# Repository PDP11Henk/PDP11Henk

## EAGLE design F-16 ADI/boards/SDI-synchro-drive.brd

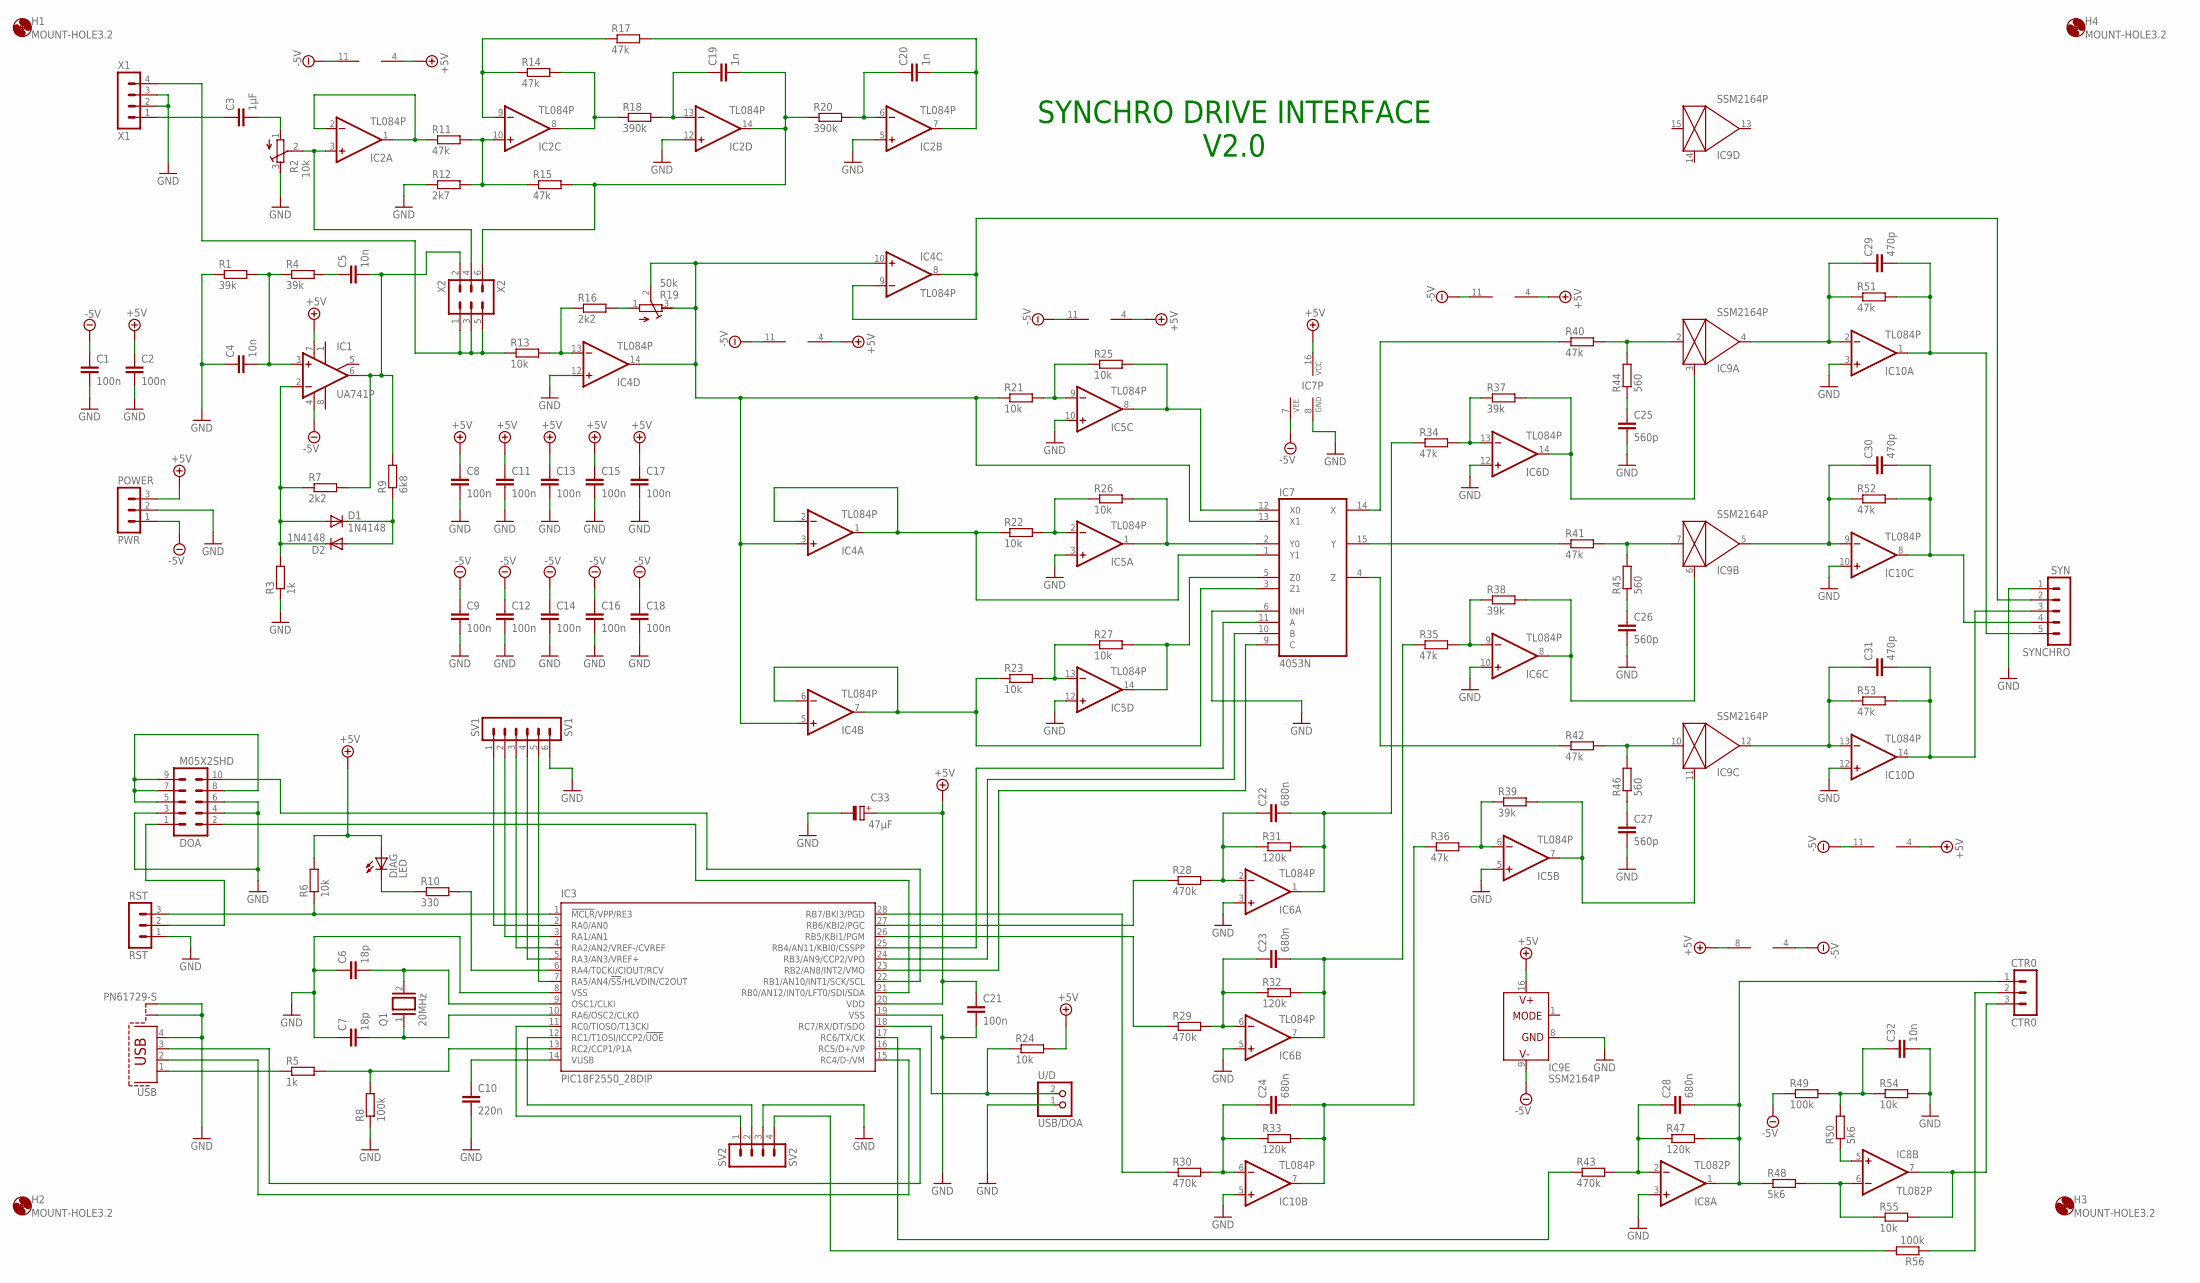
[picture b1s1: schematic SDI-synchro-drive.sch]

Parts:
C1, C2, C8, C9, C11, C12, C13, C14, C15, C16, C17, C18, C21: 100n; C025-025X050
C3: 1µF; C5B3
C4, C5, C32: 10n; C025-025X050
C6, C7: 18p; C025-025X050
C10: 220n; C5B3
C19, C20: 1n; C025-025X050
C22, C23, C24, C28: 680n; C5B3
C25, C26, C27: 560p; C025-025X050
C29, C30, C31: 470p; C025-025X050
C33: 47µF; E2,5-6
CTR0: CTR0; MA03-1
D1, D2: 1N4148; DO35-7
DIAG: LED; LED3MM
DOA: M05X2SHD; 2X5-SHROUDED
H1, H2, H3, H4: MOUNT-HOLE3.2; 3,2
IC1: UA741P; DIL08
IC2, IC4, IC5, IC6, IC10: TL084P; DIL14
IC3: PIC18F2550_28DIP; DIL28-3
IC7: 4053N; DIL16
IC8: TL082P; DIL08
IC9: SSM2164P; DIL16
POWER: PWR; MA03-1
Q1: 20MHz; QS
R1, R4, R37, R38, R39: 39k; 0204/7
R2: 10k; RTRIM3299W
R3, R5: 1k; 0204/7
R6, R13, R21, R22, R23, R24, R25, R26, R27, R54, R55: 10k; 0204/7
R7, R16: 2k2; 0204/7
R8, R49, R56: 100k; 0204/7
R9: 6k8; 0204/7
R10: 330; 0204/7
R11, R14, R15, R17, R34, R35, R36, R40, R41, R42, R51, R52, R53: 47k; 0204/7
R12: 2k7; 0204/7
R18, R20: 390k; 0204/7
R19: 50k; RTRIM3299W
R28, R29, R30, R43: 470k; 0204/7
R31, R32, R33, R47: 120k; 0204/7
R44, R45, R46: 560; 0204/7
R48, R50: 5k6; 0204/7
RST: RST; MA03-1
SV1: SV1; MA06-1
SV2: SV2; MA04-1
SYNCHRO: SYN; MA05-1
USB: PN61729-S
USB/DOA: U/D; 1X02
X1: X1; MA04-1
X2: X2; MA03-2

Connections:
+5V: C2.1, C8.1, C11.1, C13.1, C15.1, C17.1, C21.1, C33.+, DIAG.A, IC1.7 (V+), IC2.4 (V+), IC3.20 (VDD), IC4.4 (V+), IC5.4 (V+), IC6.4 (V+), IC7.16 (VCC), IC8.8 (V+), IC9.16 (V+), IC10.4 (V+), POWER.3, R6.2, R24.2
-5V: C1.1, C9.1, C12.1, C14.1, C16.1, C18.1, IC1.4 (V-), IC2.11 (V-), IC4.11 (V-), IC5.11 (V-), IC6.11 (V-), IC7.7 (VEE), IC8.4 (V-), IC9.9 (V-), IC10.11 (V-), POWER.1, R49.1
GND: C1.2, C2.2, C4.1, C6.1, C7.1, C8.2, C9.2, C10.2, C11.2, C12.2, C13.2, C14.2, C15.2, C16.2, C17.2, C18.2, C21.2, C25.2, C26.2, C27.2, C32.2, C33.-, DOA.3, DOA.4, DOA.6, IC2.5 (+IN), IC2.12 (+IN), IC3.8 (VSS), IC3.19 (VSS), IC4.12 (+IN), IC5.3 (+IN), IC5.5 (+IN), IC5.10 (+IN), IC5.12 (+IN), IC6.3 (+IN), IC6.5 (+IN), IC6.10 (+IN), IC6.12 (+IN), IC7.6 (INH), IC7.8 (GND), IC8.3 (+IN), IC9.8 (GND), IC10.3 (+IN), IC10.5 (+IN), IC10.10 (+IN), IC10.12 (+IN), POWER.2, R1.1, R2.3 (A), R3.1, R8.1, R12.1, R54.2, RST.1, SV1.6, SV2.3, SYNCHRO.1, USB.4, USB.S1, USB.S2, USB/DOA.1, X1.2, X1.3
unnamed: IC8.6 (-IN), R48.2, R55.1
unnamed: CTR0.3, IC8.7 (OUT), R55.2
unnamed: C3.2, R2.1 (E)
unnamed: IC2.3 (+IN), R2.2 (S), X2.4
unnamed: IC2.1 (OUT), IC2.2 (-IN), R11.1
unnamed: IC2.10 (+IN), R11.2, R12.2, R15.1
unnamed: C20.1, IC2.6 (-IN), R20.2
unnamed: IC2.9 (-IN), R14.1, R17.1
unnamed: IC2.8 (OUT), R14.2, R18.1
unnamed: C19.1, IC2.13 (-IN), R18.2
unnamed: C19.2, IC2.14 (OUT), R15.2, R20.1, X2.6
unnamed: C20.2, IC2.7 (OUT), R17.2
unnamed: R13.1, X1.4, X2.1, X2.3, X2.5
unnamed: IC4.13 (-IN), R13.2, R16.1
unnamed: R16.2, R19.1 (E)
unnamed: IC5.13 (-IN), R23.2, R27.1
unnamed: IC4.8 (OUT), IC4.9 (-IN), SYNCHRO.2
unnamed: CTR0.2, R56.1
unnamed: IC5.2 (-IN), R22.2, R26.1
unnamed: C5.2, IC1.6 (OUT), R7.2, R9.2, X2.2
unnamed: IC5.9 (-IN), R21.2, R25.1
unnamed: C5.1, R4.2
unnamed: IC5.8 (OUT), IC7.12 (X0), R25.2
unnamed: IC5.1 (OUT), IC7.2 (Y0), R26.2
unnamed: C4.2, IC1.3 (+IN), R1.2, R4.1
unnamed: IC5.14 (OUT), IC7.5 (Z0), R27.2
unnamed: D1.A, D2.C, IC1.2 (-IN), R3.2, R7.1
unnamed: D1.C, D2.A, R9.1
unnamed: IC7.14 (X), R40.1
unnamed: IC9.2 (IN), R40.2, R44.2
unnamed: IC7.15 (Y), R41.1
unnamed: IC9.7 (IN), R41.2, R45.2
unnamed: IC7.4 (Z), R42.1
unnamed: IC9.10 (IN), R42.2, R46.2
unnamed: C25.1, R44.1
unnamed: C26.1, R45.1
unnamed: C27.1, R46.1
unnamed: IC5.6 (-IN), R36.2, R39.1
unnamed: IC5.7 (OUT), IC9.11 (CTRL), R39.2
unnamed: IC6.14 (OUT), IC9.3 (CTRL), R37.2
unnamed: IC6.8 (OUT), IC9.6 (CTRL), R38.2
unnamed: IC6.9 (-IN), R35.2, R38.1
unnamed: IC6.13 (-IN), R34.2, R37.1
unnamed: C22.1, IC6.2 (-IN), R28.2, R31.1
unnamed: C22.2, IC6.1 (OUT), R31.2, R34.1
unnamed: C23.1, IC6.6 (-IN), R29.2, R32.1
unnamed: C23.2, IC6.7 (OUT), R32.2, R35.1
unnamed: C10.1, IC3.14 (VUSB)
unnamed: C24.1, IC10.6 (-IN), R30.2, R33.1
unnamed: C24.2, IC10.7 (OUT), R33.2, R36.1
unnamed: IC3.16 (RC5/D+/VP), USB.3
unnamed: C29.1, IC9.4 (OUT), IC10.2 (-IN), R51.1
unnamed: C29.2, IC10.1 (OUT), R51.2, SYNCHRO.5
unnamed: C30.1, IC9.5 (OUT), IC10.9 (-IN), R52.1
unnamed: C30.2, IC10.8 (OUT), R52.2, SYNCHRO.4
unnamed: C31.1, IC9.12 (OUT), IC10.13 (-IN), R53.1
unnamed: C31.2, IC10.14 (OUT), R53.2, SYNCHRO.3
unnamed: IC3.15 (RC4/D-/VM), USB.2
unnamed: R5.1, USB.1
unnamed: IC3.13 (RC2/CCP1/P1A), R5.2, R8.2
unnamed: DOA.1, RST.2
unnamed: C7.2, IC3.10 (RA6/OSC2/CLKO), Q1.1
unnamed: C6.2, IC3.9 (OSC1/CLKI), Q1.2
unnamed: IC3.1 (!MCLR!/VPP/RE3), R6.1, RST.3
unnamed: IC3.28 (RB7/BKI3/PGD), R30.1
unnamed: IC3.26 (RB5/KBI1/PGM), R29.1
unnamed: IC3.27 (RB6/KBI2/PGC), R28.1
unnamed: DOA.5, DOA.7, DOA.8, DOA.9
unnamed: DOA.2, IC3.21 (RB0/AN12/INT0/LFT0/SDI/SDA)
unnamed: DIAG.K (C), R10.1
unnamed: IC3.6 (RA4/T0CKI/CIOUT/RCV), R10.2
unnamed: DOA.10, IC3.22 (RB1/AN10/INT1/SCK/SCL)
unnamed: IC3.18 (RC7/RX/DT/SDO), R24.1, USB/DOA.2
unnamed: IC3.12 (RC1/T1OSI/ICCP2/!UOE), SV2.2
unnamed: IC3.25 (RB4/AN11/KBI0/CSSPP), IC7.11 (A)
unnamed: IC3.24 (RB3/AN9/CCP2/VPO), IC7.10 (B)
unnamed: IC3.23 (RB2/AN8/INT2/VMO), IC7.9 (C)
unnamed: IC3.2 (RA0/AN0), SV1.1
unnamed: IC3.3 (RA1/AN1), SV1.2
unnamed: IC3.4 (RA2/AN2/VREF-/CVREF), SV1.3
unnamed: IC3.5 (RA3/AN3/VREF+), SV1.4
unnamed: IC3.7 (RA5/AN4/!SS!/HLVDIN/C2OUT), SV1.5
unnamed: IC3.11 (RC0/TIOSO/T13CKI), SV2.1
unnamed: IC3.17 (RC6/TX/CK), R43.1
unnamed: C28.1, IC8.2 (-IN), R43.2, R47.1
unnamed: C28.2, CTR0.1, IC8.1 (OUT), R47.2, R48.1
unnamed: C32.1, R49.2, R50.2, R54.1
unnamed: IC8.5 (+IN), R50.1
unnamed: C3.1, X1.1
unnamed: R56.2, SV2.4
SIN000: IC4.3 (+IN), IC4.5 (+IN), IC4.10 (+IN), IC4.14 (OUT), IC7.13 (X1), R19.2 (S), R19.3 (A), R21.1
SIN120: IC4.1 (OUT), IC4.2 (-IN), IC7.1 (Y1), R22.1
SIN240: IC4.6 (-IN), IC4.7 (OUT), IC7.3 (Z1), R23.1

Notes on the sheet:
SYNCHRO DRIVE INTERFACE V2.0

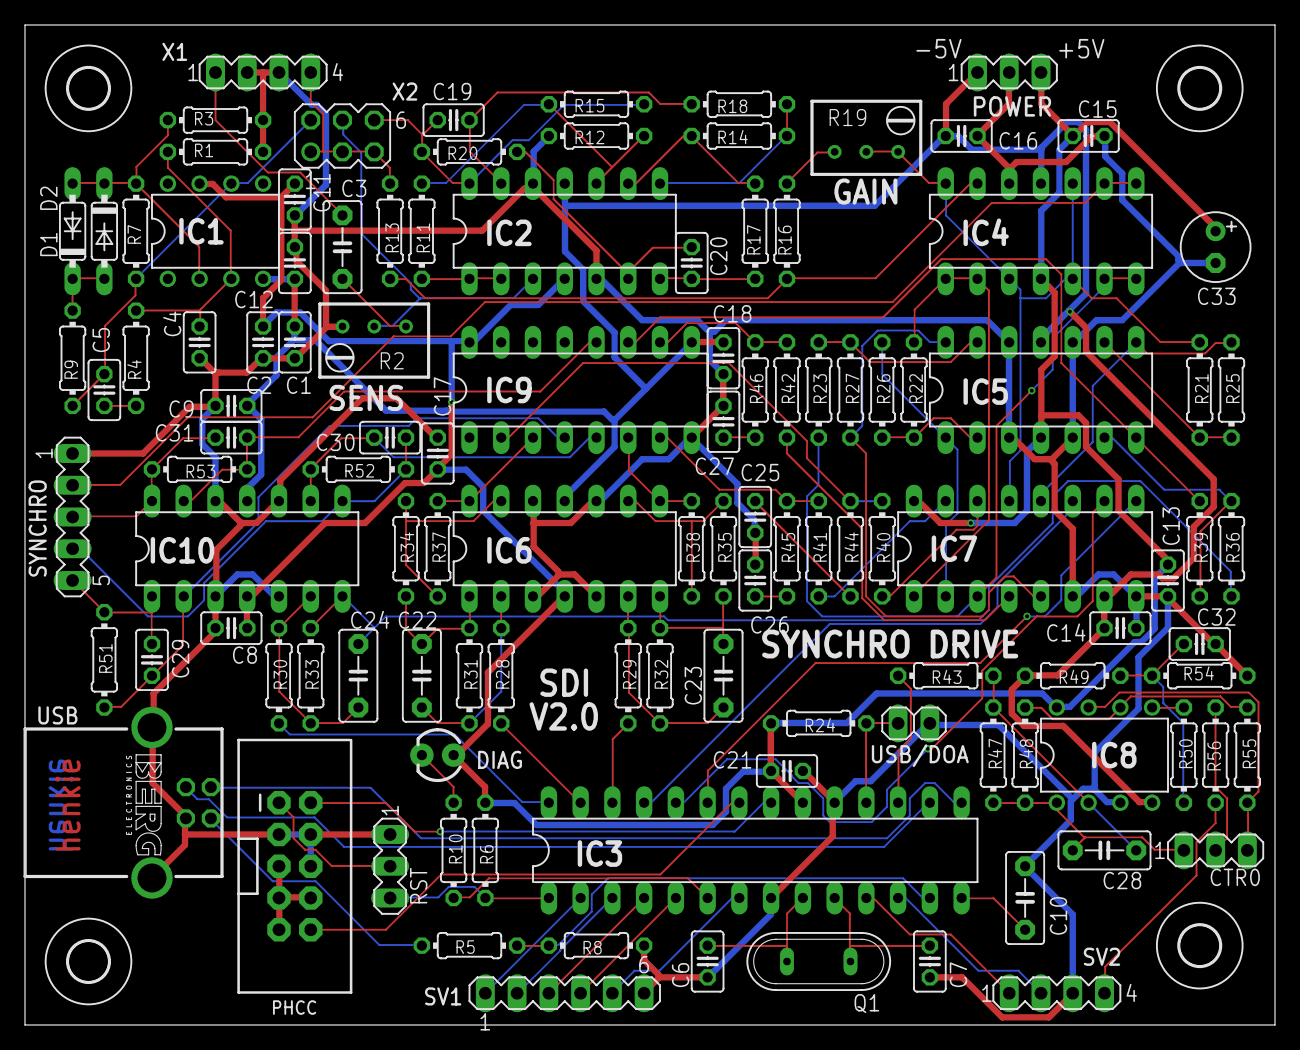
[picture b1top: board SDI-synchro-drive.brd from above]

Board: 2 copper layers, 100.0 x 80.0 mm, 118 parts (0 on the bottom side), 96 nets.

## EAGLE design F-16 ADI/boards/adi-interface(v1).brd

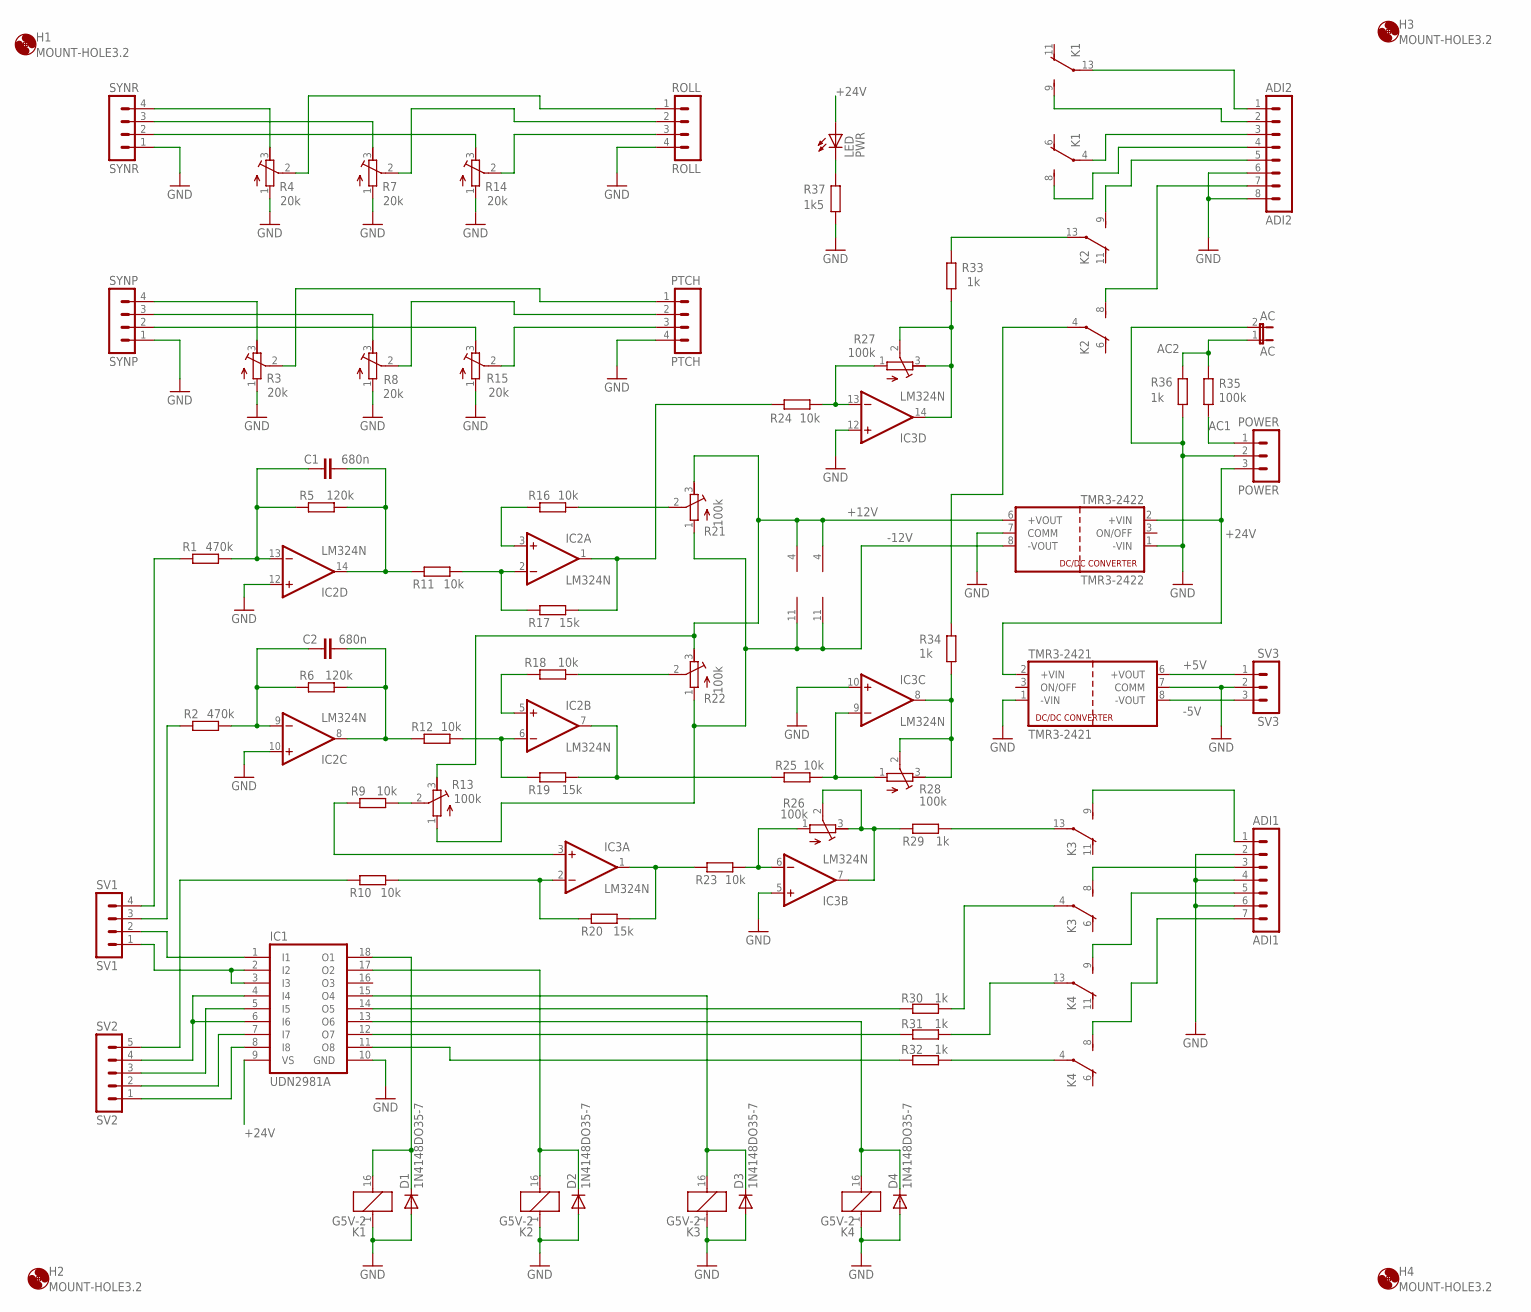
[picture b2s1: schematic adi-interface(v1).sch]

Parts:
AC: AC; 1X02
ADI1: ADI1; MA07-1
ADI2: ADI2; MA08-1
C1, C2: 680n; C050-035X075
D1, D2, D3, D4: 1N4148DO35-7; DO35-7
H1, H2, H3, H4: MOUNT-HOLE3.2; 3,2
IC1: UDN2981A; DIL18
IC2, IC3: LM324N; DIL14
K1, K2, K3, K4: G5V-2
LED: PWR; LED3MM
POWER: POWER; MA03-1
PTCH: PTCH; MA04-1
R1, R2: 470k; 0204/7
R3, R4, R7, R8, R14, R15: 20k; RTRIM64Z
R5, R6: 120k; 0204/7
R9, R10, R11, R12, R16, R18, R23, R24, R25: 10k; 0204/7
R13, R21, R22, R26, R27, R28: 100k; RTRIM64Z
R17, R19, R20: 15k; 0204/7
R29, R30, R31, R32, R33, R34, R36: 1k; 0204/7
R35: 100k; 0204/7
R37: 1k5; 0204/7
ROLL: ROLL; MA04-1
SV1: SV1; MA04-1
SV2: SV2; MA05-1
SV3: SV3; MA03-1
SYNP: SYNP; MA04-1
SYNR: SYNR; MA04-1
TMR3-2421: TMR3-2421; TRACO_SIP-8
TMR3-2422: TMR3-2422; TRACO_SIP-8

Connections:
+5V: SV3.1, TMR3-2421.6 (+VOUT)
+12V: IC2.4 (V+), IC3.4 (V+), R13.3 (E), R21.3 (E), R22.3 (E), TMR3-2422.6 (+VOUT)
+24V: IC1.9 (VS), LED.A, POWER.3, TMR3-2421.2 (+VIN), TMR3-2422.2 (+VIN)
-5V: SV3.3, TMR3-2421.8 (-VOUT)
-12V: IC2.11 (V-), IC3.11 (V-), R13.1 (A), R21.1 (A), R22.1 (A), TMR3-2422.8 (-VOUT)
AC1: POWER.1, R35.1
AC2: AC.1, R35.2, R36.2
GND: AC.2, ADI1.2, ADI1.4, ADI1.6, ADI2.6, ADI2.8, D1.A, D2.A, D3.A, D4.A, IC1.10 (GND), IC2.10 (+IN), IC2.12 (+IN), IC3.5 (+IN), IC3.10 (+IN), IC3.12 (+IN), K1.1, K2.1, K3.1, K4.1, POWER.2, PTCH.4, R3.1 (A), R4.1 (A), R7.1 (A), R8.1 (A), R14.1 (A), R15.1 (A), R36.1, R37.1, ROLL.4, SV3.2, SYNP.1, SYNR.1, TMR3-2421.1 (-VIN), TMR3-2421.7 (COMM), TMR3-2422.1 (-VIN), TMR3-2422.7 (COMM)
unnamed: R14.3 (E), SYNR.2
unnamed: R7.3 (E), SYNR.3
unnamed: R4.3 (E), SYNR.4
unnamed: R3.3 (E), SYNP.4
unnamed: R8.3 (E), SYNP.3
unnamed: R15.3 (E), SYNP.2
unnamed: R14.2 (S), ROLL.3
unnamed: R7.2 (S), ROLL.2
unnamed: R4.2 (S), ROLL.1
unnamed: PTCH.3, R15.2 (S)
unnamed: PTCH.2, R8.2 (S)
unnamed: PTCH.1, R3.2 (S)
unnamed: ADI2.1, K1.13
unnamed: ADI2.2, K1.9 (S)
unnamed: ADI2.3, K1.4
unnamed: ADI2.4, K1.8 (S)
unnamed: ADI2.5, K2.9 (S)
unnamed: ADI2.7, K2.8 (S)
unnamed: D1.C, IC1.18 (O1), K1.16 (2)
unnamed: ADI1.1, K3.9 (S)
unnamed: D2.C, IC1.17 (O2), K2.16 (2)
unnamed: ADI1.3, K3.8 (S)
unnamed: ADI1.5, K4.9 (S)
unnamed: ADI1.7, K4.8 (S)
unnamed: K3.4, R30.2
unnamed: K4.13, R31.2
unnamed: IC1.2 (I2), IC1.3 (I3), SV1.1
unnamed: IC1.1 (I1), SV1.2
unnamed: K4.4, R32.2
unnamed: D4.C, IC1.13 (O6), K4.16 (2)
unnamed: D3.C, IC1.15 (O4), K3.16 (2)
unnamed: IC1.11 (O8), R32.1
unnamed: IC1.12 (O7), R31.1
unnamed: R2.1, SV1.3
unnamed: C2.1, IC2.9 (-IN), R2.2, R6.1
unnamed: C2.2, IC2.8 (OUT), R6.2, R12.1
unnamed: R1.1, SV1.4
unnamed: IC2.2 (-IN), R11.2, R17.1
unnamed: C1.2, IC2.14 (OUT), R5.2, R11.1
unnamed: C1.1, IC2.13 (-IN), R1.2, R5.1
unnamed: K2.13, R33.2
unnamed: IC2.1 (OUT), R17.2, R24.1
unnamed: IC2.6 (-IN), R12.2, R19.1
unnamed: K2.4, R34.2
unnamed: IC2.7 (OUT), R19.2, R25.1
unnamed: IC2.3 (+IN), R16.1
unnamed: IC2.5 (+IN), R18.1
unnamed: R16.2, R21.2 (S)
unnamed: R18.2, R22.2 (S)
unnamed: LED.K (C), R37.2
unnamed: IC3.6 (-IN), R23.2, R26.1 (A)
unnamed: IC3.7 (OUT), R26.2 (S), R26.3 (E), R29.1
unnamed: IC3.13 (-IN), R24.2, R27.1 (A)
unnamed: K3.13, R29.2
unnamed: IC3.1 (OUT), R20.2, R23.1
unnamed: IC3.14 (OUT), R27.2 (S), R27.3 (E), R33.1
unnamed: R9.2, R13.2 (S)
unnamed: IC3.9 (-IN), R25.2, R28.1 (A)
unnamed: IC3.8 (OUT), R28.2 (S), R28.3 (E), R34.1
unnamed: IC3.3 (+IN), R9.1
unnamed: R10.1, SV2.5
unnamed: IC3.2 (-IN), R10.2, R20.1
unnamed: IC1.14 (O5), R30.1
unnamed: IC1.4 (I4), IC1.6 (I6), SV2.4
unnamed: IC1.5 (I5), SV2.3
unnamed: IC1.7 (I7), SV2.2
unnamed: IC1.8 (I8), SV2.1

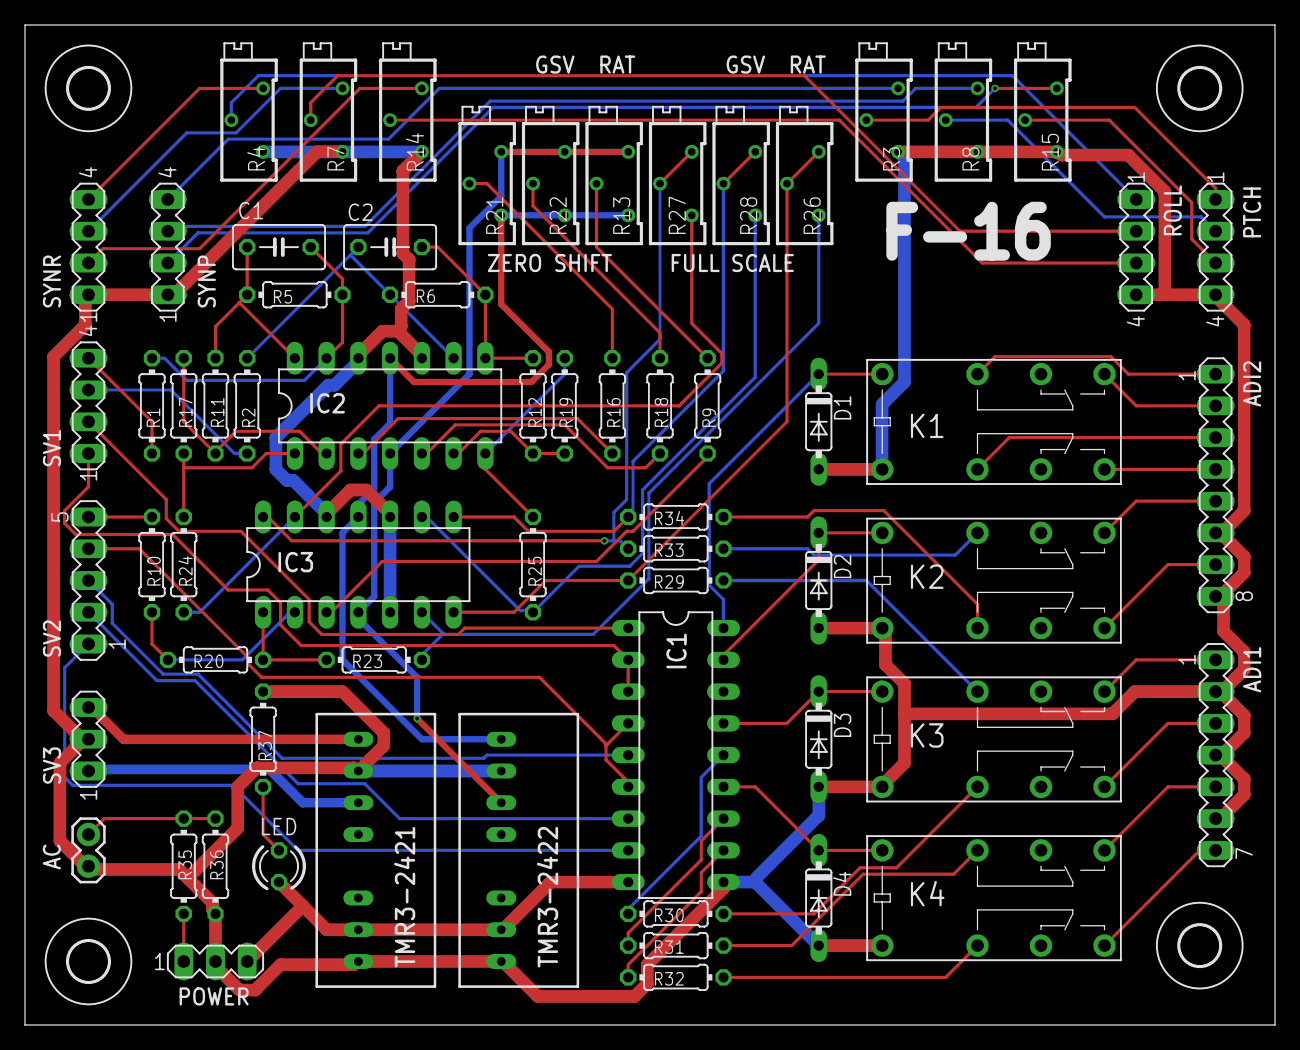
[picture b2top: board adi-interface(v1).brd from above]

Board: 2 copper layers, 100.0 x 80.0 mm, 68 parts (0 on the bottom side), 75 nets.

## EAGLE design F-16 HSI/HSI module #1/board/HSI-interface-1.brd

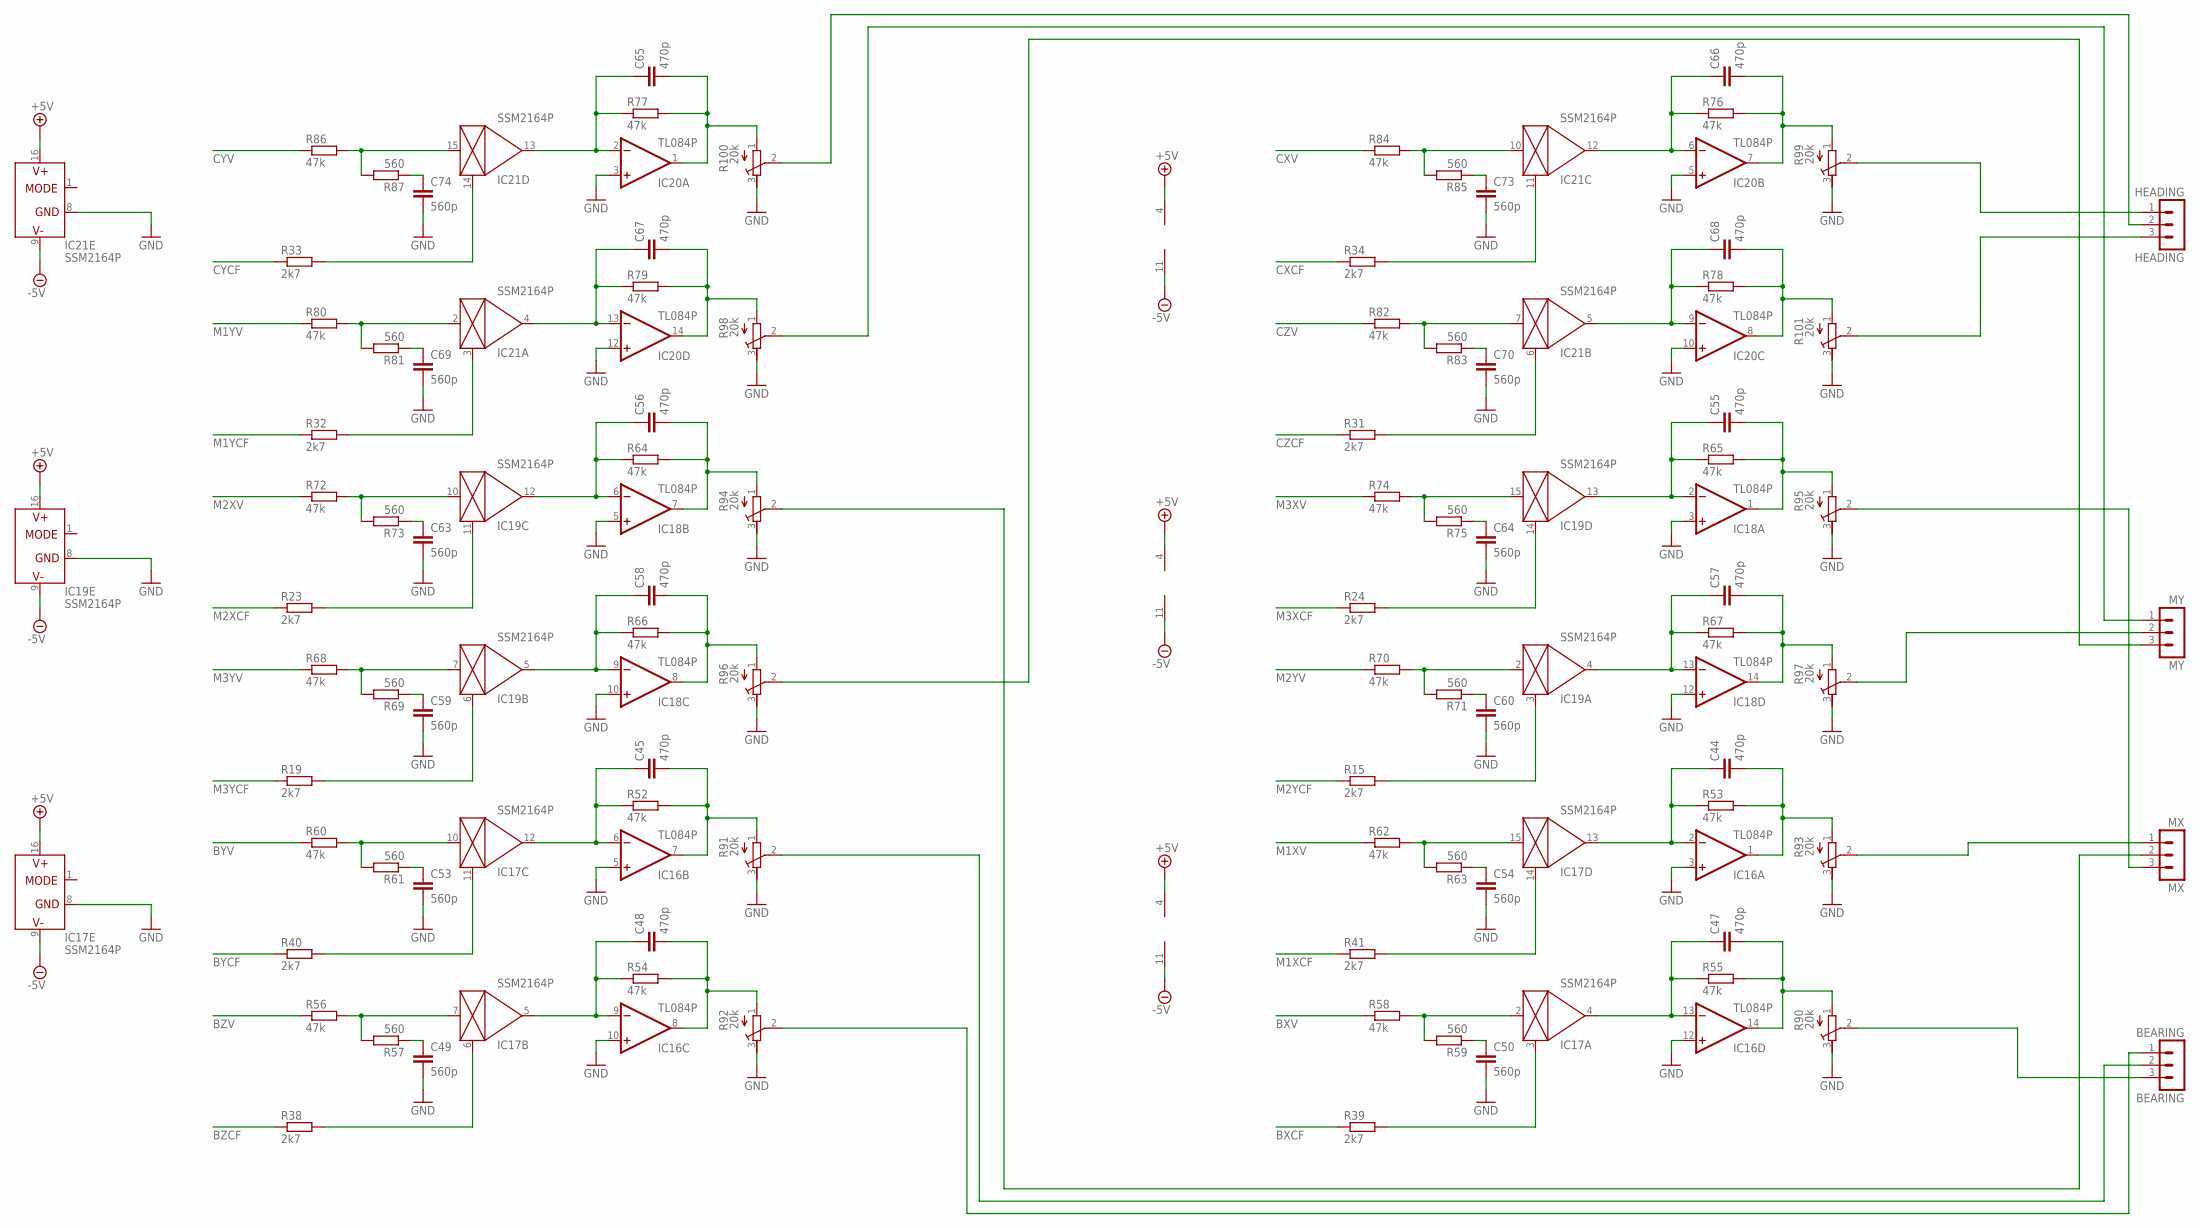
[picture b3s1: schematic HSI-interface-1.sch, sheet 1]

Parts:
BEARING: BEARING; MA03-1
C44, C45, C47, C48, C55, C56, C57, C58, C65, C66, C67, C68: 470p; C025-025X050
C49, C50, C53, C54, C59, C60, C63, C64, C69, C70, C73, C74: 560p; C025-025X050
HEADING: HEADING; MA03-1
IC16, IC18, IC20: TL084P; DIL14
IC17, IC19, IC21: SSM2164P; DIL16
MX: MX; MA03-1
MY: MY; MA03-1
R15, R19, R23, R24, R31, R32, R33, R34, R38, R39, R40, R41: 2k7; 0207/7
R52, R53, R54, R55, R56, R58, R60, R62, R64, R65, R66, R67, R68, R70, R72, R74, R76, R77, R78, R79, R80, R82, R84, R86: 47k; 0207/7
R57, R59, R61, R63, R69, R71, R73, R75, R81, R83, R85, R87: 560; 0207/7
R90, R91, R92, R93, R94, R95, R96, R97, R98, R99, R100, R101: 20k; RTRIM64Z

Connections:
+5V: IC16.4 (V+), IC17.16 (V+), IC18.4 (V+), IC19.16 (V+), IC20.4 (V+), IC21.16 (V+); also elsewhere on the board
-5V: IC16.11 (V-), IC17.9 (V-), IC18.11 (V-), IC19.9 (V-), IC20.11 (V-), IC21.9 (V-); also elsewhere on the board
BXCF: R39.1; also elsewhere on the board
BXV: R58.1; also elsewhere on the board
BYCF: R40.1; also elsewhere on the board
BYV: R60.1; also elsewhere on the board
BZCF: R38.1; also elsewhere on the board
BZV: R56.1; also elsewhere on the board
CXCF: R34.1; also elsewhere on the board
CXV: R84.1; also elsewhere on the board
CYCF: R33.1; also elsewhere on the board
CYV: R86.1; also elsewhere on the board
CZCF: R31.1; also elsewhere on the board
CZV: R82.1; also elsewhere on the board
GND: C49.2, C50.2, C53.2, C54.2, C59.2, C60.2, C63.2, C64.2, C69.2, C70.2, C73.2, C74.2, IC16.3 (+IN), IC16.5 (+IN), IC16.10 (+IN), IC16.12 (+IN), IC17.8 (GND), IC18.3 (+IN), IC18.5 (+IN), IC18.10 (+IN), IC18.12 (+IN), IC19.8 (GND), IC20.3 (+IN), IC20.5 (+IN), IC20.10 (+IN), IC20.12 (+IN), IC21.8 (GND), R90.3 (A), R91.3 (A), R92.3 (A), R93.3 (A), R94.3 (A), R95.3 (A), R96.3 (A), R97.3 (A), R98.3 (A), R99.3 (A), R100.3 (A), R101.3 (A); also elsewhere on the board
M1XCF: R41.1; also elsewhere on the board
M1XV: R62.1; also elsewhere on the board
M1YCF: R32.1; also elsewhere on the board
M1YV: R80.1; also elsewhere on the board
M2XCF: R23.1; also elsewhere on the board
M2XV: R72.1; also elsewhere on the board
M2YCF: R15.1; also elsewhere on the board
M2YV: R70.1; also elsewhere on the board
M3XCF: R24.1; also elsewhere on the board
M3XV: R74.1; also elsewhere on the board
M3YCF: R19.1; also elsewhere on the board
M3YV: R68.1; also elsewhere on the board
unnamed: IC21.3 (CTRL), R32.2
unnamed: IC21.14 (CTRL), R33.2
unnamed: IC19.11 (CTRL), R23.2
unnamed: IC19.6 (CTRL), R19.2
unnamed: IC17.11 (CTRL), R40.2
unnamed: IC17.6 (CTRL), R38.2
unnamed: IC21.11 (CTRL), R34.2
unnamed: IC21.6 (CTRL), R31.2
unnamed: IC19.14 (CTRL), R24.2
unnamed: IC19.3 (CTRL), R15.2
unnamed: IC17.14 (CTRL), R41.2
unnamed: IC17.3 (CTRL), R39.2
unnamed: IC21.10 (IN), R84.2, R85.2
unnamed: C73.1, R85.1
unnamed: IC21.15 (IN), R86.2, R87.2
unnamed: C74.1, R87.1
unnamed: IC21.7 (IN), R82.2, R83.2
unnamed: C70.1, R83.1
unnamed: IC21.2 (IN), R80.2, R81.2
unnamed: C69.1, R81.1
unnamed: C67.1, IC20.13 (-IN), IC21.4 (OUT), R79.1
unnamed: C65.1, IC20.2 (-IN), IC21.13 (OUT), R77.1
unnamed: C66.1, IC20.6 (-IN), IC21.12 (OUT), R76.1
unnamed: C68.1, IC20.9 (-IN), IC21.5 (OUT), R78.1
unnamed: C66.2, IC20.7 (OUT), R76.2, R99.1 (E)
unnamed: C65.2, IC20.1 (OUT), R77.2, R100.1 (E)
unnamed: C68.2, IC20.8 (OUT), R78.2, R101.1 (E)
unnamed: C67.2, IC20.14 (OUT), R79.2, R98.1 (E)
unnamed: IC19.10 (IN), R72.2, R73.2
unnamed: C63.1, R73.1
unnamed: IC19.15 (IN), R74.2, R75.2
unnamed: C64.1, R75.1
unnamed: IC19.2 (IN), R70.2, R71.2
unnamed: C60.1, R71.1
unnamed: IC19.7 (IN), R68.2, R69.2
unnamed: C59.1, R69.1
unnamed: C57.1, IC18.13 (-IN), IC19.4 (OUT), R67.1
unnamed: C58.1, IC18.9 (-IN), IC19.5 (OUT), R66.1
unnamed: C55.1, IC18.2 (-IN), IC19.13 (OUT), R65.1
unnamed: C56.1, IC18.6 (-IN), IC19.12 (OUT), R64.1
unnamed: C58.2, IC18.8 (OUT), R66.2, R96.1 (E)
unnamed: C57.2, IC18.14 (OUT), R67.2, R97.1 (E)
unnamed: C56.2, IC18.7 (OUT), R64.2, R94.1 (E)
unnamed: C55.2, IC18.1 (OUT), R65.2, R95.1 (E)
unnamed: HEADING.1, R99.2 (S)
unnamed: HEADING.3, R101.2 (S)
unnamed: HEADING.2, R100.2 (S)
unnamed: MY.1, R98.2 (S)
unnamed: MY.3, R96.2 (S)
unnamed: MY.2, R97.2 (S)
unnamed: MX.3, R95.2 (S)
unnamed: MX.2, R94.2 (S)
unnamed: IC17.10 (IN), R60.2, R61.2
unnamed: C53.1, R61.1
unnamed: IC17.15 (IN), R62.2, R63.2
unnamed: C54.1, R63.1
unnamed: IC17.2 (IN), R58.2, R59.2
unnamed: C50.1, R59.1
unnamed: IC17.7 (IN), R56.2, R57.2
unnamed: C49.1, R57.1
unnamed: C44.1, IC16.2 (-IN), IC17.13 (OUT), R53.1
unnamed: C47.1, IC16.13 (-IN), IC17.4 (OUT), R55.1
unnamed: MX.1, R93.2 (S)
unnamed: C45.1, IC16.6 (-IN), IC17.12 (OUT), R52.1
unnamed: C48.1, IC16.9 (-IN), IC17.5 (OUT), R54.1
unnamed: C45.2, IC16.7 (OUT), R52.2, R91.1 (E)
unnamed: C44.2, IC16.1 (OUT), R53.2, R93.1 (E)
unnamed: C48.2, IC16.8 (OUT), R54.2, R92.1 (E)
unnamed: C47.2, IC16.14 (OUT), R55.2, R90.1 (E)
unnamed: BEARING.3, R90.2 (S)
unnamed: BEARING.1, R92.2 (S)
unnamed: BEARING.2, R91.2 (S)

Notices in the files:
parts and their libraries:
henk: Licensing: CC v3.0 Share-Alike You are welcome to use this library for commercial purposes.
